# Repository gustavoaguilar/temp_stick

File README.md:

# temp_stick
Simple device to take temperature measurements

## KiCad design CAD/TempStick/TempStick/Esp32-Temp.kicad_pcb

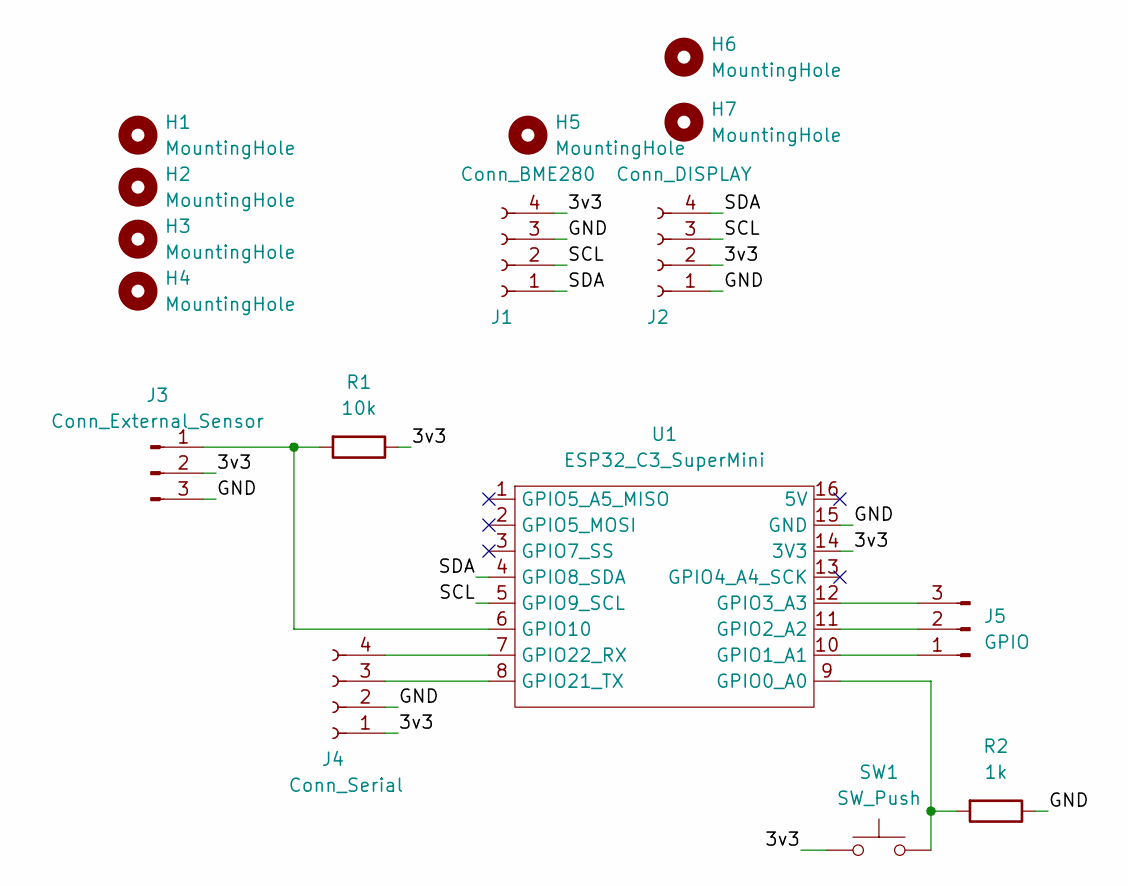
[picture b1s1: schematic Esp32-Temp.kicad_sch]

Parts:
H1, H2, H3, H4: MountingHole; MountingHole_3.2mm_M3
H5, H6, H7: MountingHole; MountingHole_3.5mm
J1: Conn_BME280; PinHeader_1x04_P2.54mm_Vertical
J2: Conn_DISPLAY; PinHeader_1x04_P2.54mm_Vertical
J3: Conn_External_Sensor; PinHeader_1x03_P2.54mm_Horizontal
J4: Conn_Serial; PinHeader_1x04_P2.54mm_Horizontal
J5: GPIO; PinHeader_1x03_P2.54mm_Horizontal
R1: 10k; R_Axial_DIN0207_L6.3mm_D2.5mm_P10.16mm_Horizontal
R2: 1k; R_Axial_DIN0207_L6.3mm_D2.5mm_P10.16mm_Horizontal
SW1: SW_Push; SW_PUSH_6mm
U1: ESP32_C3_SuperMini

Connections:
/3v3: J1.4, J2.2, J3.2, J4.1, R1.1, SW1.1, U1.14 (3V3)
/GND: J1.3, J2.1, J3.3, J4.2, R2.1, U1.15 (GND)
/SCL: J1.2, J2.3, U1.5 (GPIO9_SCL)
/SDA: J1.1, J2.4, U1.4 (GPIO8_SDA)
unnamed: J3.1, R1.2, U1.6 (GPIO10)
unnamed: J4.3, U1.8 (GPIO21_TX)
unnamed: J4.4, U1.7 (GPIO22_RX)
unnamed: J5.1, U1.10 (GPIO1_A1)
unnamed: J5.2, U1.11 (GPIO2_A2)
unnamed: J5.3, U1.12 (GPIO3_A3)
unnamed: R2.2, SW1.2, U1.9 (GPIO0_A0)

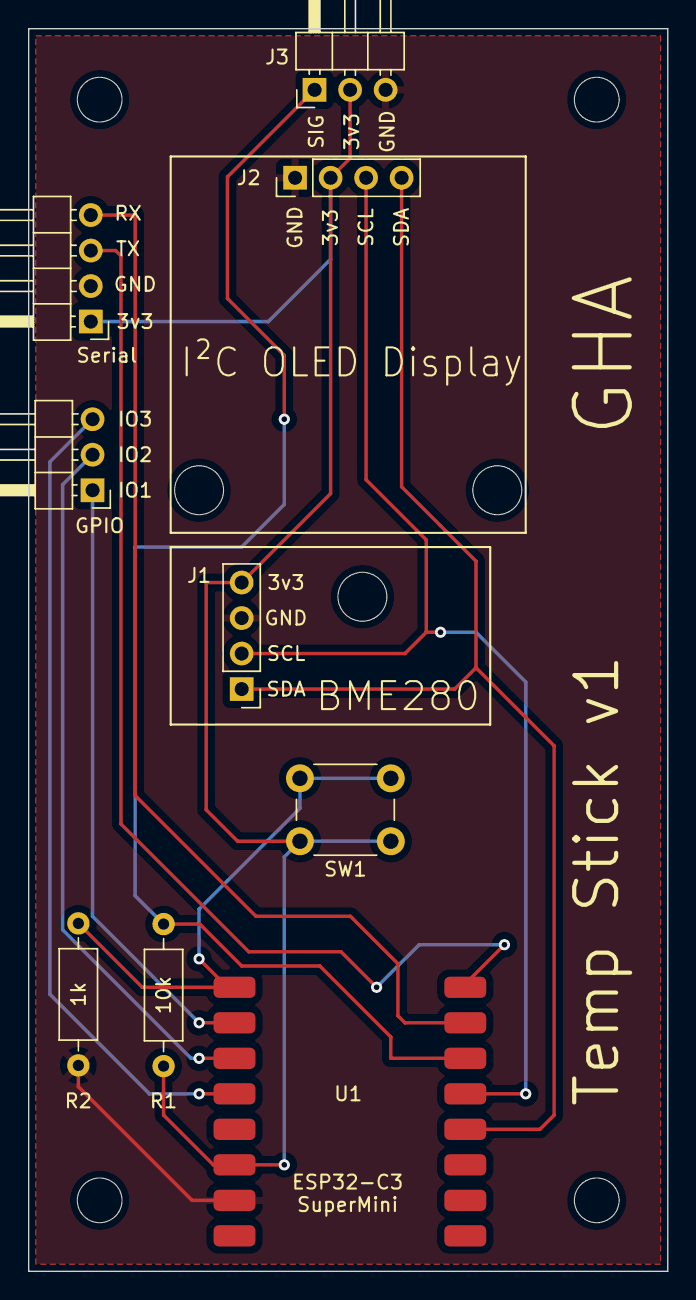
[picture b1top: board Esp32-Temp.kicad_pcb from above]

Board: 2 copper layers, 45.7 x 88.9 mm, 16 parts (0 on the bottom side), 11 nets.

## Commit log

2024-01-08 Better python software
2024-01-08 Added cpp tests and raylib version
2024-01-11 Added partial csv generation
2024-01-14 Changed to new ESP32 module
2024-01-14 Added gitignore
2024-01-14 Created device class
2024-03-12 Added screen off
2024-03-21 Added simple logger functionality
2024-03-21 Clean files and add build script
2024-03-21 Added TryOpenFile
    Added more debug prints
2024-03-22 Fix path of device
    Add cleaning of buffer before read
    Remove -v flag from build script
2024-03-28 Added a simulator for development
2024-03-28 Improved testing
    Now the data is parsed by the device class
2024-04-02 Changed file locations
2024-04-04 Added service file
2024-04-04 Added basic graph generation
2024-04-21 Fix no data on probe
2024-04-22 Disabled default test mode Fix 1 minute counter
2024-04-22 Added timeststamp in the logger
2024-05-13 Moved python software to a directory
2024-05-16 Added more test cases to the simulator
2024-05-16 Added simple software in C
2024-07-14 Added new Cpp project
2024-07-14 Updated gitignore
